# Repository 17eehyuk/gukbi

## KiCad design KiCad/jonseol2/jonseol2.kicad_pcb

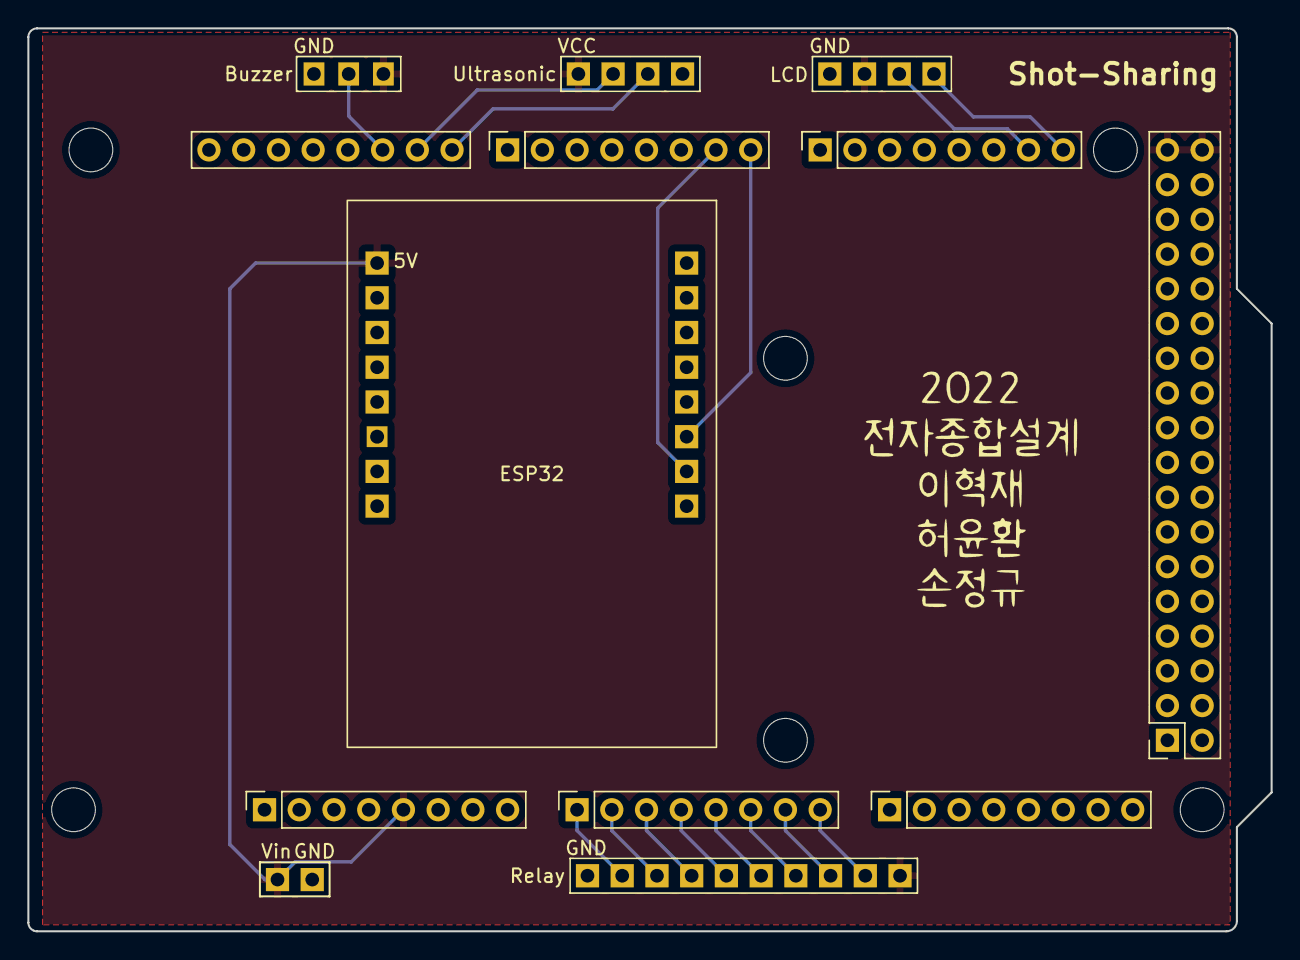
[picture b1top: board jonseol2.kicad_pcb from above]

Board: 2 copper layers, 90.9 x 66.0 mm, 18 parts (0 on the bottom side), 17 nets.

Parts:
B1: Buzzer; MH_FMD_Buzzer
Display1: LCD; DM43_LCD_Module
E1: ESP32
J1: Power; PinSocket_1x08_P2.54mm_Vertical
J2, J3: Analog; PinSocket_1x08_P2.54mm_Vertical
J4: Digital; PinSocket_2x18_P2.54mm_Vertical
J5: PWM; PinSocket_1x10_P2.54mm_Vertical
J6: PWM; PinSocket_1x08_P2.54mm_Vertical
J7: Communication; PinSocket_1x08_P2.54mm_Vertical
MH1, MH2, MH3, MH4, MH5, MH6: MountingHole_3.2mm
R1: Relay; 8_channel_relay
U1: Ultrasonic; ultrasonic_sensor

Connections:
+5V: B1.3 (VCC), Display1.2 (VCC), E1.1 (5V), J1.5, J4.35, J4.36, R1.10 (VCC), U1.1 (VCC)
Buzzer: B1.2 (I/O), J5.8
Echo: J5.10, U1.3 (Echo)
GND: B1.1 (GND), Display1.1 (GND), E1.2 (GND), J1.6, J1.7, J4.1, J4.2, J5.4, R1.1 (GND), U1.4 (GND)
RX: E1.11 (RX), J6.8
Relay_1: J2.1, R1.2 (IN1)
Relay_2: J2.2, R1.3 (IN2)
Relay_3: J2.3, R1.4 (IN3)
Relay_4: J2.4, R1.5 (IN4)
Relay_5: J2.5, R1.6 (IN5)
Relay_6: J2.6, R1.7 (IN6)
Relay_7: J2.7, R1.8 (IN7)
Relay_8: J2.8, R1.9 (IN8)
SCL: Display1.4 (SCL), J7.8
SDA: Display1.3 (SDA), J7.7
TX: E1.10 (TX), J6.7
Trig: J5.9, U1.2 (Trig)

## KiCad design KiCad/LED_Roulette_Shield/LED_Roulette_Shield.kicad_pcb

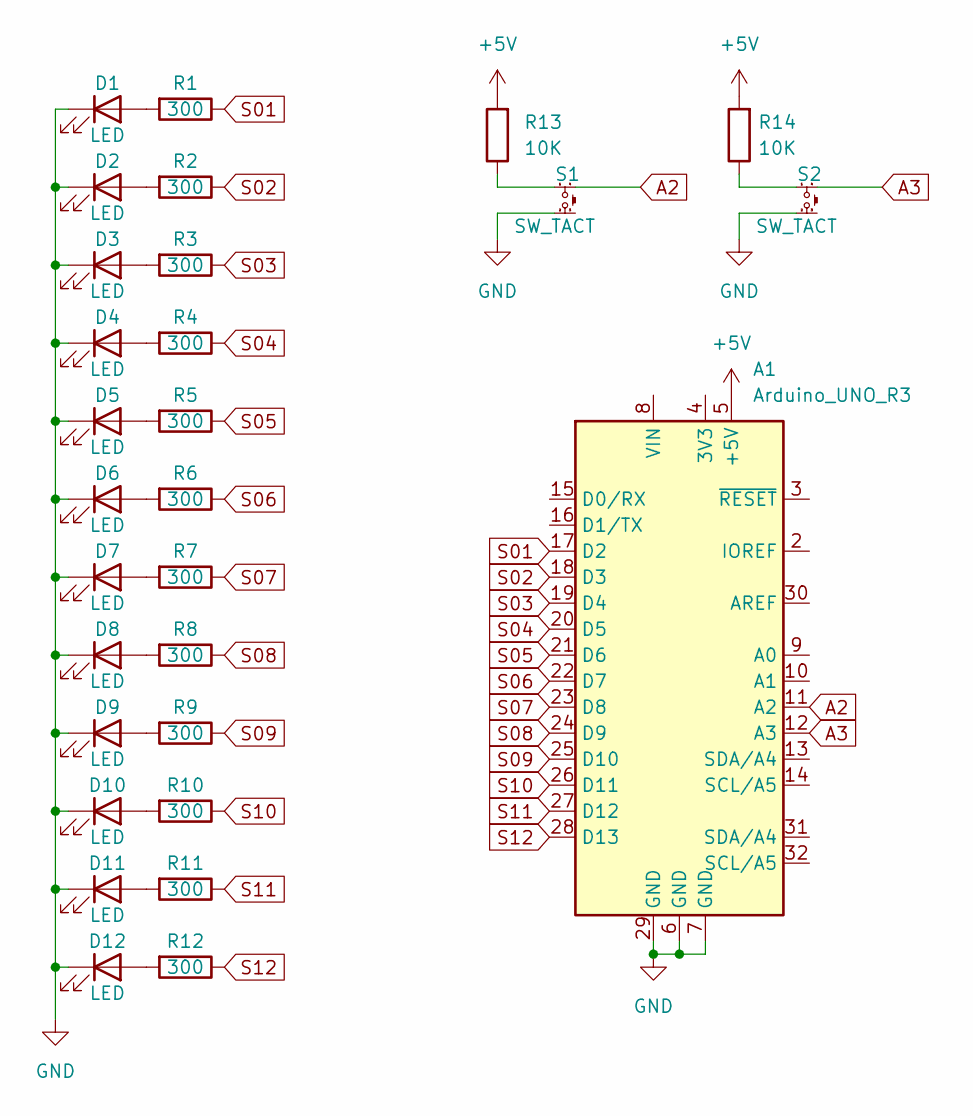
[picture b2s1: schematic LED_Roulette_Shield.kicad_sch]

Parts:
A1: Arduino_UNO_R3
D1, D2, D3, D4, D5, D6, D7, D8, D9, D10, D11, D12: LED; LED_D5.0mm
R1, R2, R3, R4, R5, R6, R7, R8, R9, R10, R11, R12: 300; R_Axial_DIN0207_L6.3mm_D2.5mm_P7.62mm_Horizontal
R13, R14: 10K; R_Axial_DIN0207_L6.3mm_D2.5mm_P7.62mm_Horizontal
S1, S2: SW_TACT; NW3-TS-G008

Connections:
+5V: A1.5 (+5V), R13.2, R14.2
A2: A1.11 (A2), S1.4
A3: A1.12 (A3), S2.4
GND: A1.6 (GND), A1.7 (GND), A1.29 (GND), D1.1 (K), D2.1 (K), D3.1 (K), D4.1 (K), D5.1 (K), D6.1 (K), D7.1 (K), D8.1 (K), D9.1 (K), D10.1 (K), D11.1 (K), D12.1 (K), S1.2, S2.2
unnamed: D1.2 (A), R1.2
unnamed: D2.2 (A), R2.2
unnamed: D3.2 (A), R3.2
unnamed: D4.2 (A), R4.2
unnamed: D5.2 (A), R5.2
unnamed: D6.2 (A), R6.2
unnamed: D7.2 (A), R7.2
unnamed: D8.2 (A), R8.2
unnamed: D9.2 (A), R9.2
unnamed: D10.2 (A), R10.2
unnamed: D11.2 (A), R11.2
unnamed: D12.2 (A), R12.2
unnamed: R13.1, S1.1
unnamed: R14.1, S2.1
S01: A1.17 (D2), R1.1
S02: A1.18 (D3), R2.1
S03: A1.19 (D4), R3.1
S04: A1.20 (D5), R4.1
S05: A1.21 (D6), R5.1
S06: A1.22 (D7), R6.1
S07: A1.23 (D8), R7.1
S08: A1.24 (D9), R8.1
S09: A1.25 (D10), R9.1
S10: A1.26 (D11), R10.1
S11: A1.27 (D12), R11.1
S12: A1.28 (D13), R12.1

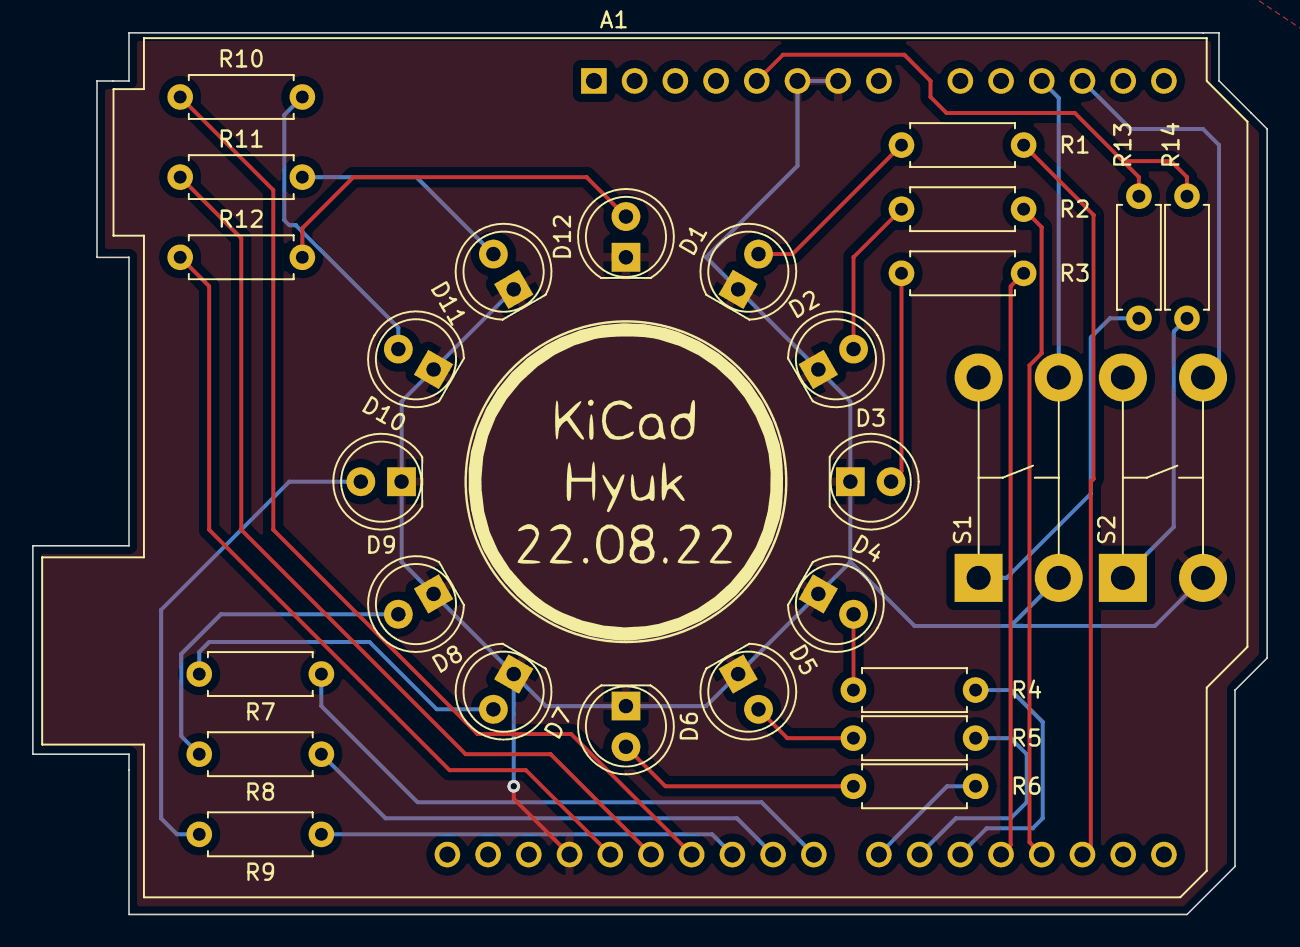
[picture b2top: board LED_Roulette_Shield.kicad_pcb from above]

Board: 2 copper layers, 77.0 x 55.0 mm, 29 parts (0 on the bottom side), 30 nets.

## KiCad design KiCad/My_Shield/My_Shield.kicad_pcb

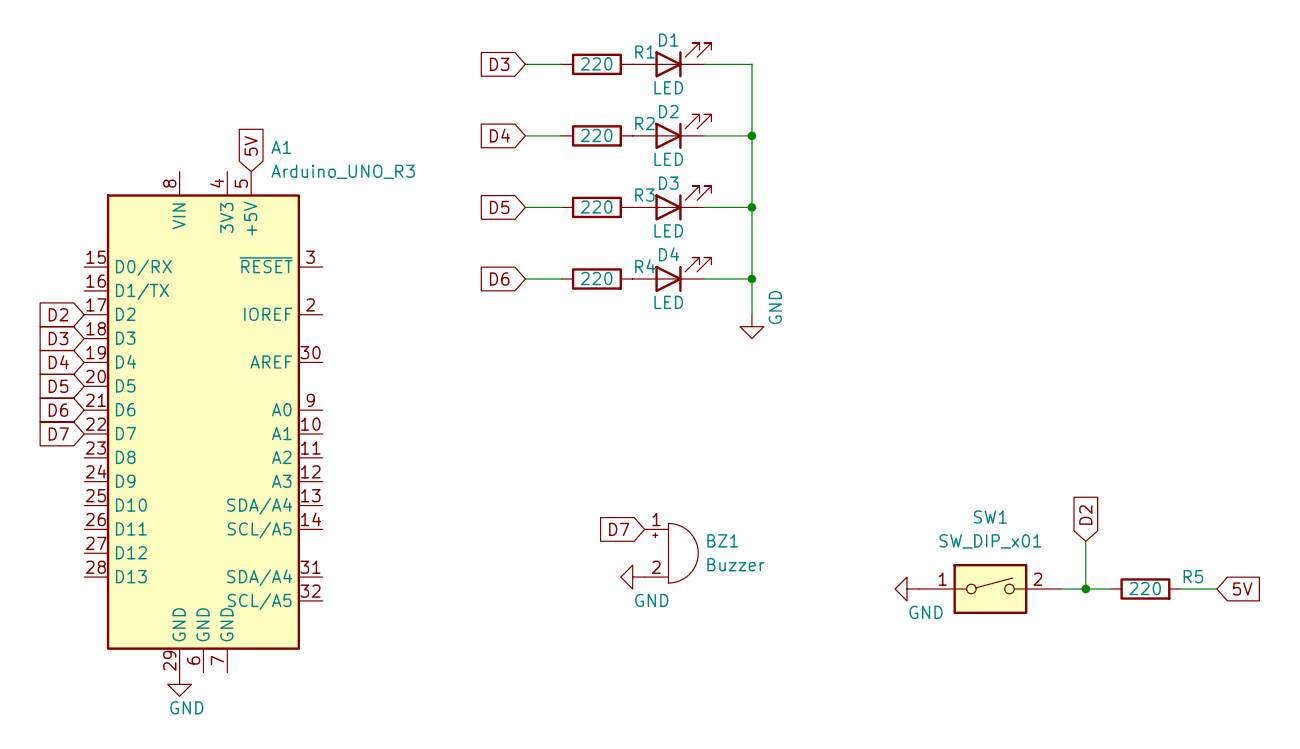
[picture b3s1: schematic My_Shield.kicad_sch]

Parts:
A1: Arduino_UNO_R3
BZ1: Buzzer; Buzzer_12x9.5RM7.6
D1, D2, D3, D4: LED; LED_D5.0mm
R1, R2, R3, R4, R5: 220; R_Axial_DIN0207_L6.3mm_D2.5mm_P7.62mm_Horizontal
SW1: SW_DIP_x01; SW_DIP_SPSTx01_Slide_9.78x4.72mm_W7.62mm_P2.54mm

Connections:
5V: A1.5 (+5V), R5.2
D2: A1.17 (D2), R5.1, SW1.2
D3: A1.18 (D3), R1.1
D4: A1.19 (D4), R2.1
D5: A1.20 (D5), R3.1
D6: A1.21 (D6), R4.1
D7: A1.22 (D7), BZ1.1 (-)
GND: A1.29 (GND), BZ1.2 (+), D1.1 (K), D2.1 (K), D3.1 (K), D4.1 (K), SW1.1
unnamed: D1.2 (A), R1.2
unnamed: D2.2 (A), R2.2
unnamed: D3.2 (A), R3.2
unnamed: D4.2 (A), R4.2

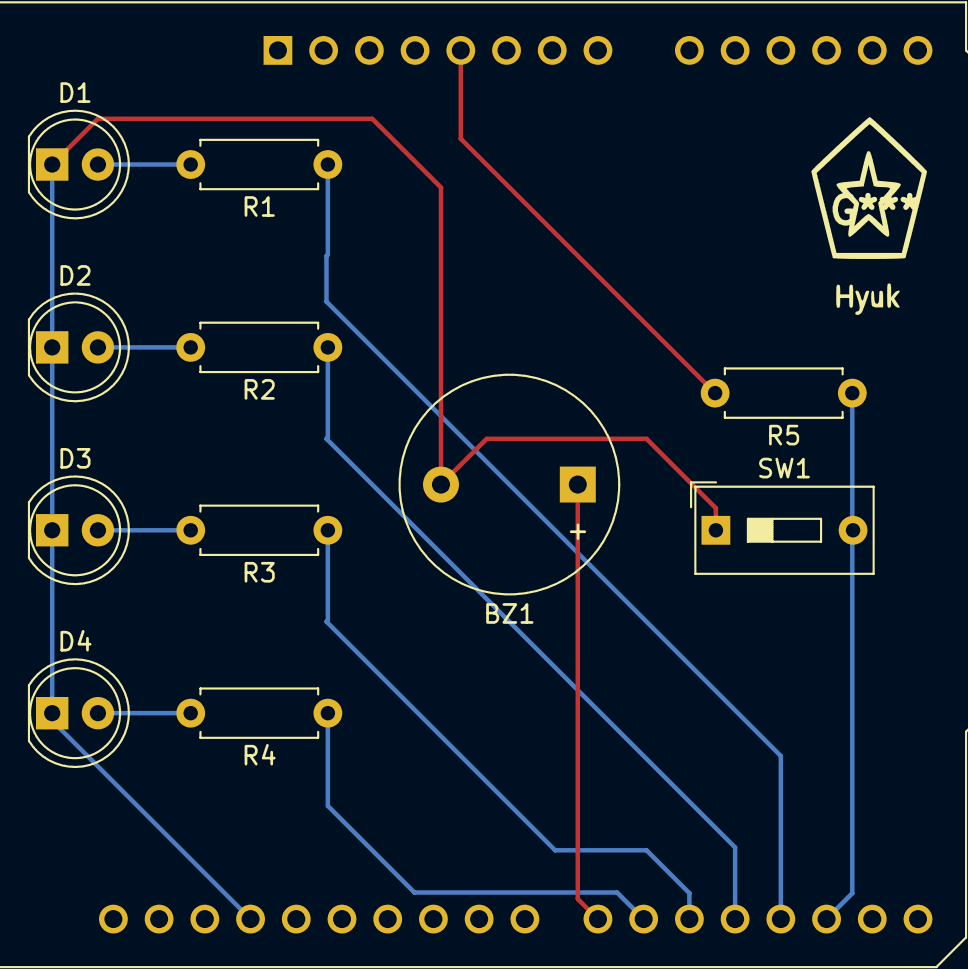
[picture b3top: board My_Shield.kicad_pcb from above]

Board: 2 copper layers, 12 parts (0 on the bottom side), 12 nets.

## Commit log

2022-07-26 220726_1136
2022-07-26 %date %time
2022-07-26 time
2022-07-26 2022-07-26_12:05:55.39
2022-07-26 2022-07-26_12:06:30.35
2022-07-26 2022-07-26_17:31:11.05
2022-07-26 2022-07-26_17:51:16.42
2022-07-27 2022-07-27_11:00:42.97
2022-07-27 2022-07-27_14:37:09.40
2022-07-27 2022-07-27_16:41:35.72
2022-08-02 2022-08-02_10:22:21.85
2022-08-02 2022-08-02_10:22:48.08
2022-08-02 2022-08-02_15:47:08.34
2022-08-03 2022-08-03_14:26:52.52
2022-08-08 2022-08-08_17:20:52.81
2022-08-08 2022-08-08_17:30:25.11
2022-08-09 2022-08-09_14:42:12.32
2022-08-09 2022-08-09_16:38:17.89
2022-08-10 2022-08-10_17:08:27.52
2022-08-17 2022-08-17_19:11:59.77
2022-08-19 2022-08-19_15:12:09.83
2022-08-19 2022-08-19_15:12:40.16
2022-08-22 2022-08-22_21:09:50.41
2022-08-23 2022-08-23_15:05:18.90
2022-08-23 2022-08-23_19:21:33.30
2022-08-26 2022-08-26_14:39:03.96
2022-08-26 2022-08-26_16:56:07.63
2022-08-29 2022-08-29_16:13:09.50
2022-09-05 2022-09-05_17:31:53.18
2022-09-06 2022-09-06_17:31:50.91
2022-09-06 2022-09-06_23:20:56.56
2022-09-07 2022-09-07_15:03:23.49
